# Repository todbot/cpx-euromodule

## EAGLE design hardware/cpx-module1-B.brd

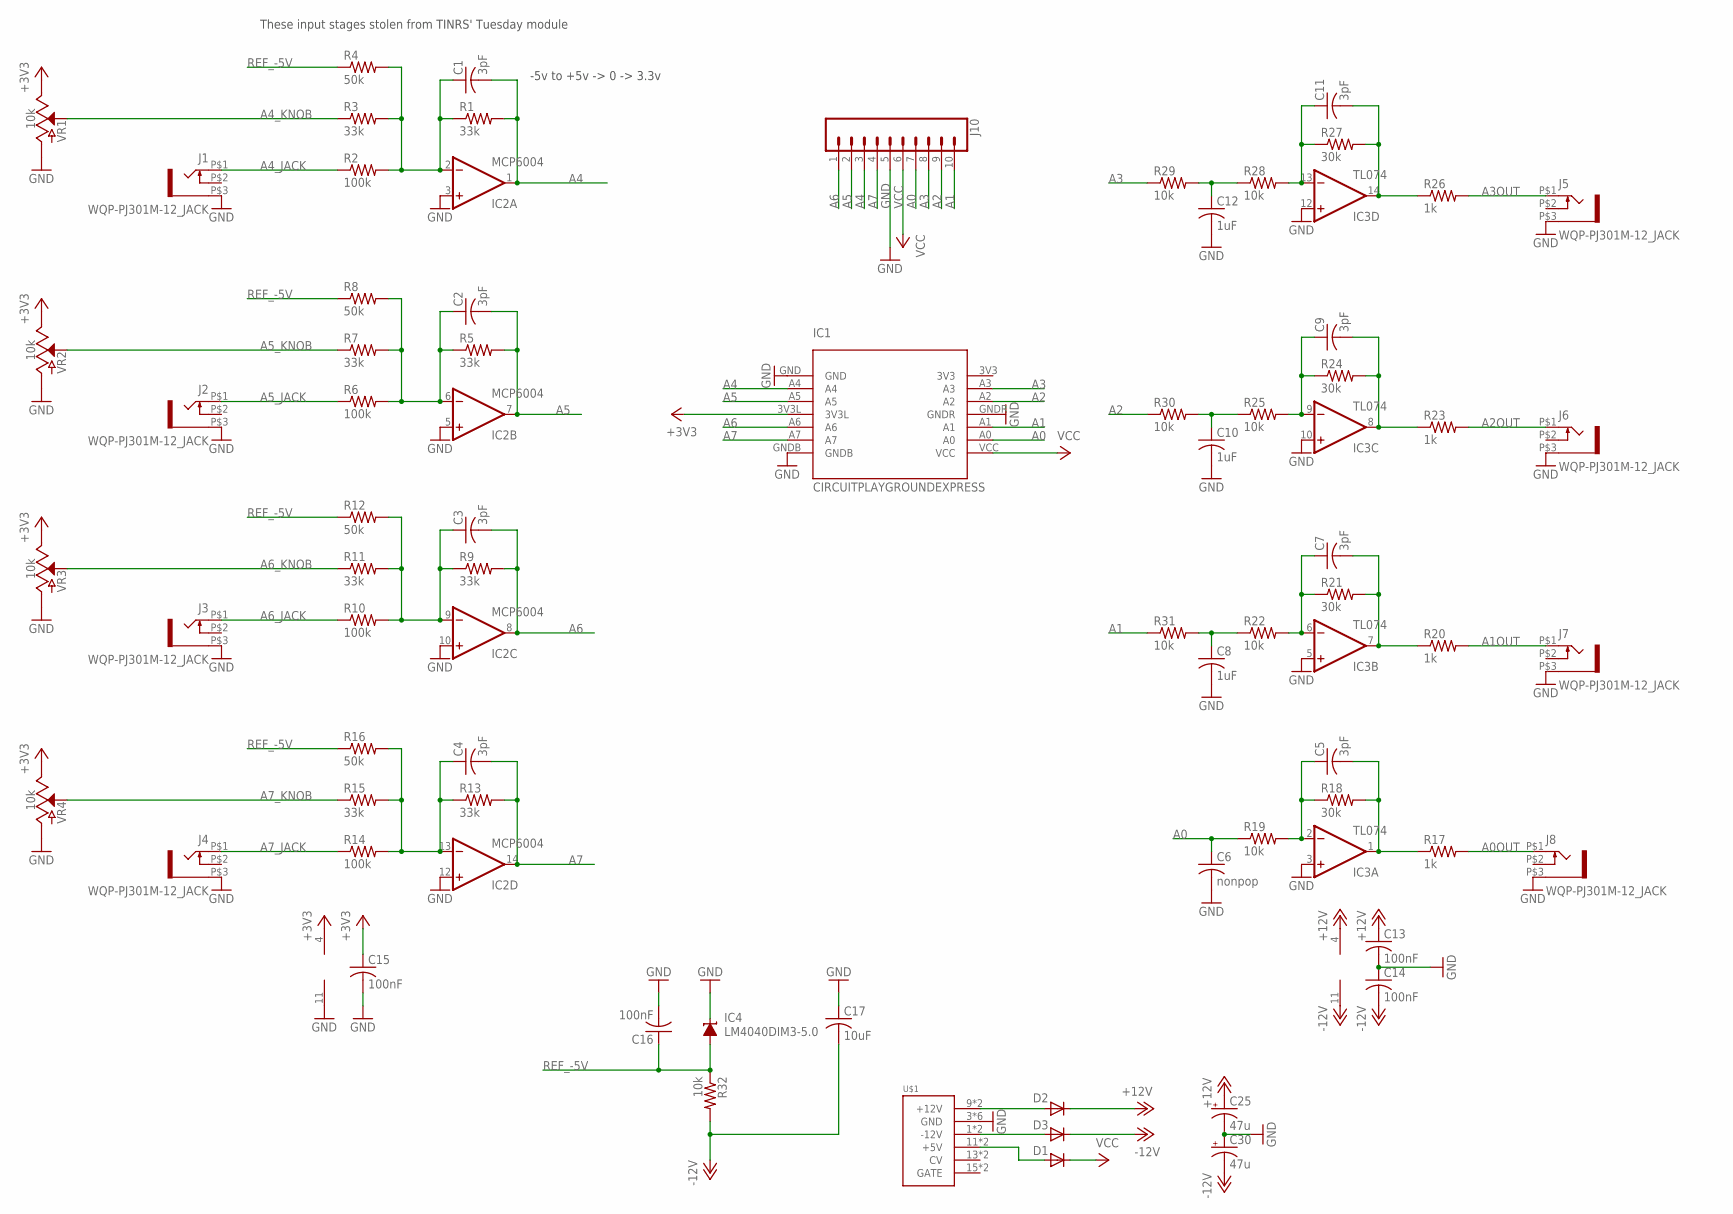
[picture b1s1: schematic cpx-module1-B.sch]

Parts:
C1, C2, C3, C4, C5, C7, C9, C11: 3pF; C0603
C6: nonpop; C0603
C8, C10, C12: 1uF; C0603
C13, C14, C15, C16: 100nF; C0603
C17: 10uF; C0603
C25, C30: 47u; PANASONIC_D
D1, D2, D3: 1N5819HW; SOD123
IC1: CIRCUITPLAYGROUNDEXPRESS
IC2: MCP6004; SO14
IC3: TL074; SO14
IC4: LM4040DIM3-5.0; DBZ_R-PDSO-G3
J1, J2, J3, J4, J5, J6, J7, J8: WQP-PJ301M-12_JACK
J10: CONN_10"; 1X10
R1, R3, R5, R7, R9, R11, R13, R15: 33k; R0603
R2, R6, R10, R14: 100k; R0603
R4, R8, R12, R16: 50k; R0603
R17, R20, R23, R26: 1k; R0603
R18, R21, R24, R27: 30k; R0603
R19, R22, R25, R28, R29, R30, R31, R32: 10k; R0603
U$1: POWER; POWER_16
VR1, VR2, VR3, VR4: 10k; POT-PTH-ALPS-KIT

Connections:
+3V3: C15.1, IC1.3V3L, IC2.4 (V+), VR1.P$1 (E), VR2.P$1 (E), VR3.P$1 (E), VR4.P$1 (E)
+12V: C13.1, C25.+, D2.C, IC3.4 (V+)
-12V: C14.2, C17.2, C30.-, D3.C, IC3.11 (V-), R32.2
A0: C6.1, IC1.A0, J10.7, R19.1
A0OUT: J8.P$1 (2), R17.2
A1: IC1.A1, J10.10, R31.1
A1OUT: J7.P$1 (2), R20.2
A2: IC1.A2, J10.9, R30.1
A2OUT: J6.P$1 (2), R23.2
A3: IC1.A3, J10.8, R29.1
A3OUT: J5.P$1 (2), R26.2
A4: C1.2, IC1.A4, IC2.1 (OUT), J10.3, R1.2
A4_JACK: J1.P$1 (2), R2.1
A4_KNOB: R3.1, VR1.P$2 (S)
A5: C2.2, IC1.A5, IC2.7 (OUT), J10.2, R5.2
A5_JACK: J2.P$1 (2), R6.1
A5_KNOB: R7.1, VR2.P$2 (S)
A6: C3.2, IC1.A6, IC2.8 (OUT), J10.1, R9.2
A6_JACK: J3.P$1 (2), R10.1
A6_KNOB: R11.1, VR3.P$2 (S)
A7: C4.2, IC1.A7, IC2.14 (OUT), J10.4, R13.2
A7_JACK: J4.P$1 (2), R14.1
A7_KNOB: R15.1, VR4.P$2 (S)
GND: C6.2, C8.2, C10.2, C12.2, C13.2, C14.1, C15.2, C16.2, C17.1, C25.-, C30.+, IC1.GND, IC1.GNDB, IC1.GNDR, IC2.3 (+IN), IC2.5 (+IN), IC2.10 (+IN), IC2.11 (V-), IC2.12 (+IN), IC3.3 (+IN), IC3.5 (+IN), IC3.10 (+IN), IC3.12 (+IN), IC4.1 (C), J1.P$3 (1), J2.P$3 (1), J3.P$3 (1), J4.P$3 (1), J5.P$3 (1), J6.P$3 (1), J7.P$3 (1), J8.P$3 (1), J10.5, U$1.3 (GND), U$1.4 (GND), U$1.5 (GND), U$1.6 (GND), U$1.7 (GND), U$1.8 (GND), VR1.P$3 (A), VR2.P$3 (A), VR3.P$3 (A), VR4.P$3 (A)
unnamed: C5.2, IC3.1 (OUT), R17.1, R18.2
unnamed: C2.1, IC2.6 (-IN), R5.1, R6.2, R7.2, R8.2
unnamed: C3.1, IC2.9 (-IN), R9.1, R10.2, R11.2, R12.2
unnamed: C4.1, IC2.13 (-IN), R13.1, R14.2, R15.2, R16.2
unnamed: C1.1, IC2.2 (-IN), R1.1, R2.2, R3.2, R4.2
unnamed: C5.1, IC3.2 (-IN), R18.1, R19.2
unnamed: C7.2, IC3.7 (OUT), R20.1, R21.2
unnamed: C7.1, IC3.6 (-IN), R21.1, R22.2
unnamed: C9.2, IC3.8 (OUT), R23.1, R24.2
unnamed: C9.1, IC3.9 (-IN), R24.1, R25.2
unnamed: C11.2, IC3.14 (OUT), R26.1, R27.2
unnamed: C11.1, IC3.13 (-IN), R27.1, R28.2
unnamed: D2.A, U$1.9 (+12V), U$1.10 (+12V)
unnamed: D3.A, U$1.1 (-12V), U$1.2 (-12V)
unnamed: D1.A, U$1.11 (+5V), U$1.12 (+5V)
unnamed: C12.1, R28.1, R29.2
unnamed: C10.1, R25.1, R30.2
unnamed: C8.1, R22.1, R31.2
REF_-5V: C16.1, IC4.2 (A), R4.1, R8.1, R12.1, R16.1, R32.1
VCC: D1.C, IC1.VCC, J10.6

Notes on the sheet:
-5v to +5v -> 0 -> 3.3v
These input stages stolen from TINRS' Tuesday module

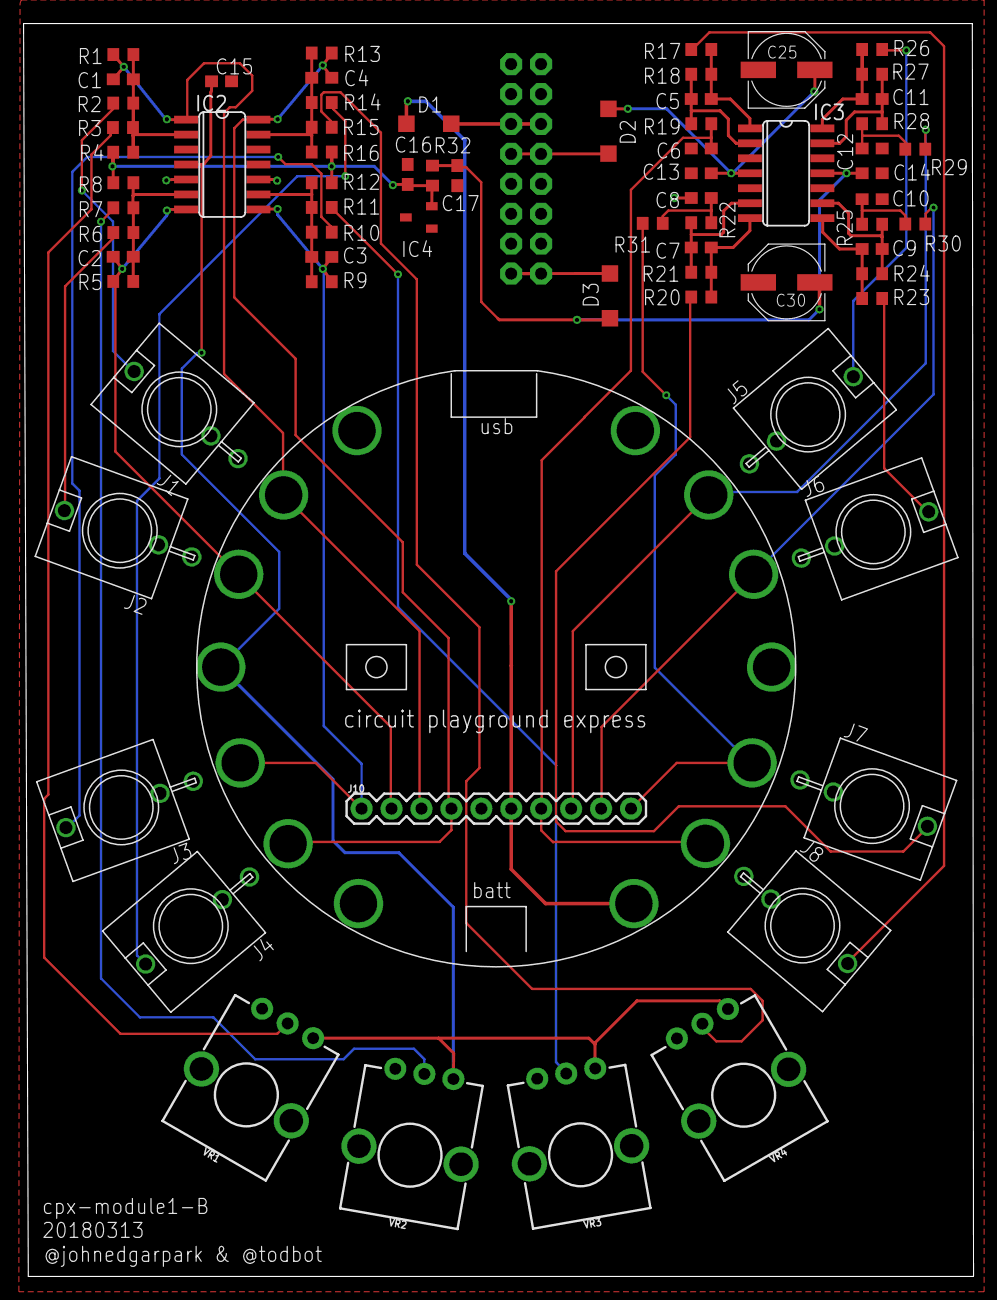
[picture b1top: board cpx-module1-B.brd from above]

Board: 2 copper layers, 80.6 x 106.3 mm, 72 parts (1 on the bottom side), 44 nets.

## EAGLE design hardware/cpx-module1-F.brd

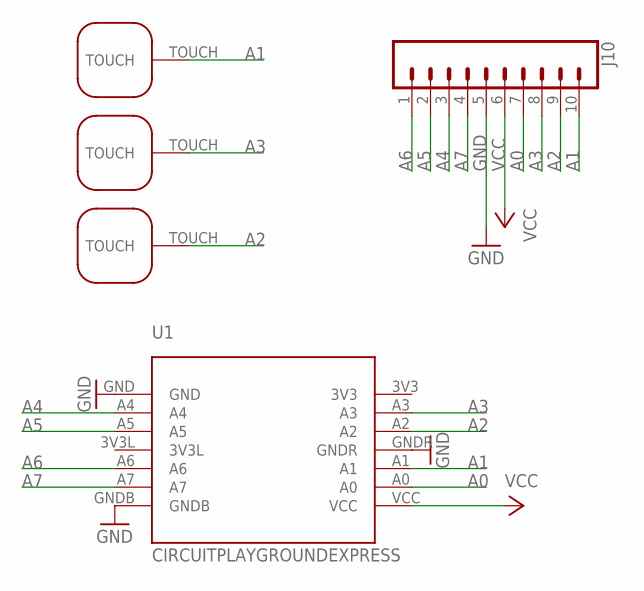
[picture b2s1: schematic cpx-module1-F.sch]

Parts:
J10: CONN_10"; 1X10
T1, T2, T4: TOUCHPADROUND1; TOUCHPAD1
U1: CIRCUITPLAYGROUNDEXPRESS

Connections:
A0: J10.7, U1.A0
A1: J10.10, T2.TOUCH, U1.A1
A2: J10.9, T4.TOUCH, U1.A2
A3: J10.8, T1.TOUCH, U1.A3
A4: J10.3, U1.A4
A5: J10.2, U1.A5
A6: J10.1, U1.A6
A7: J10.4, U1.A7
GND: J10.5, U1.GND, U1.GNDB, U1.GNDR
VCC: J10.6, U1.VCC

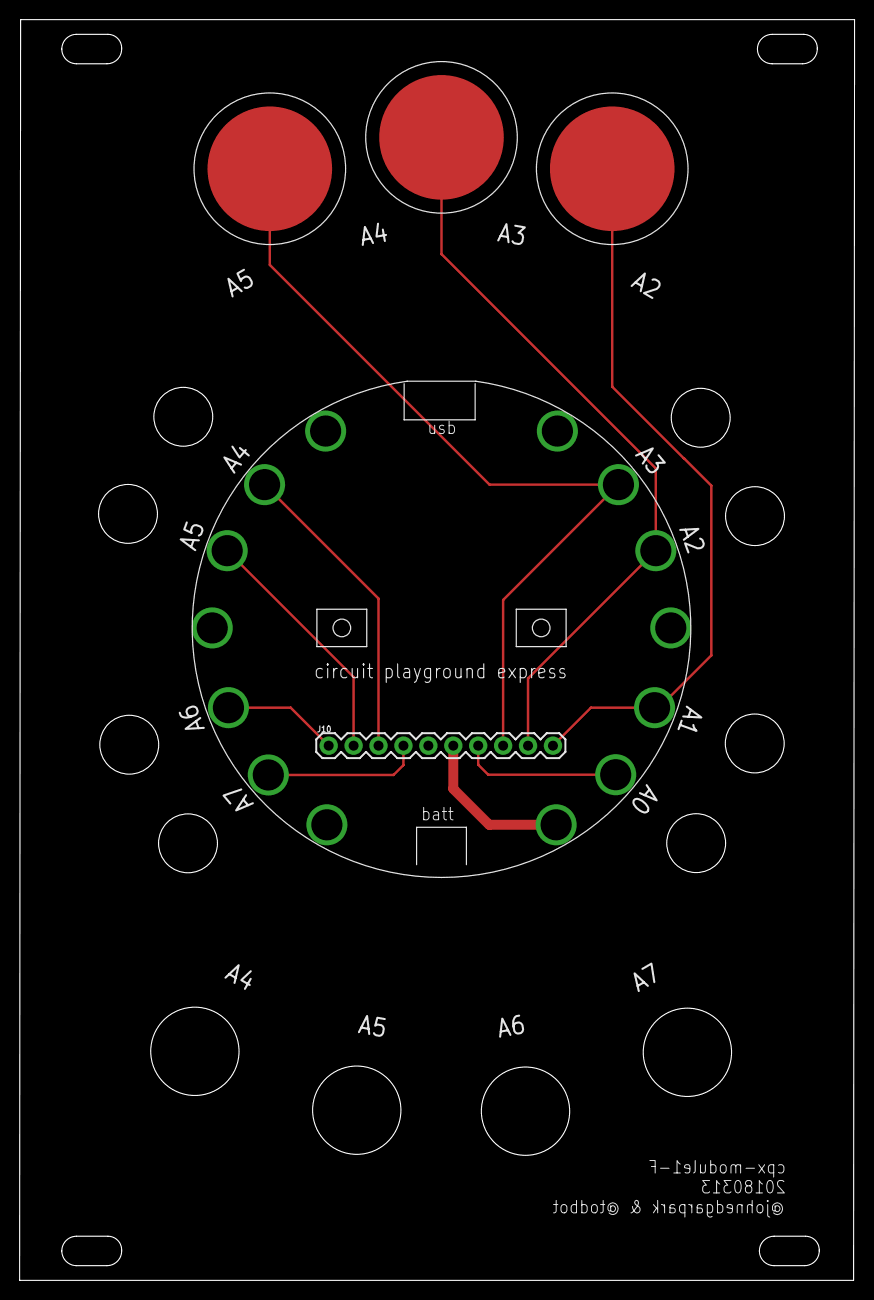
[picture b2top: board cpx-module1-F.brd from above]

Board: 2 copper layers, 85.1 x 128.5 mm, 5 parts (0 on the bottom side), 10 nets.

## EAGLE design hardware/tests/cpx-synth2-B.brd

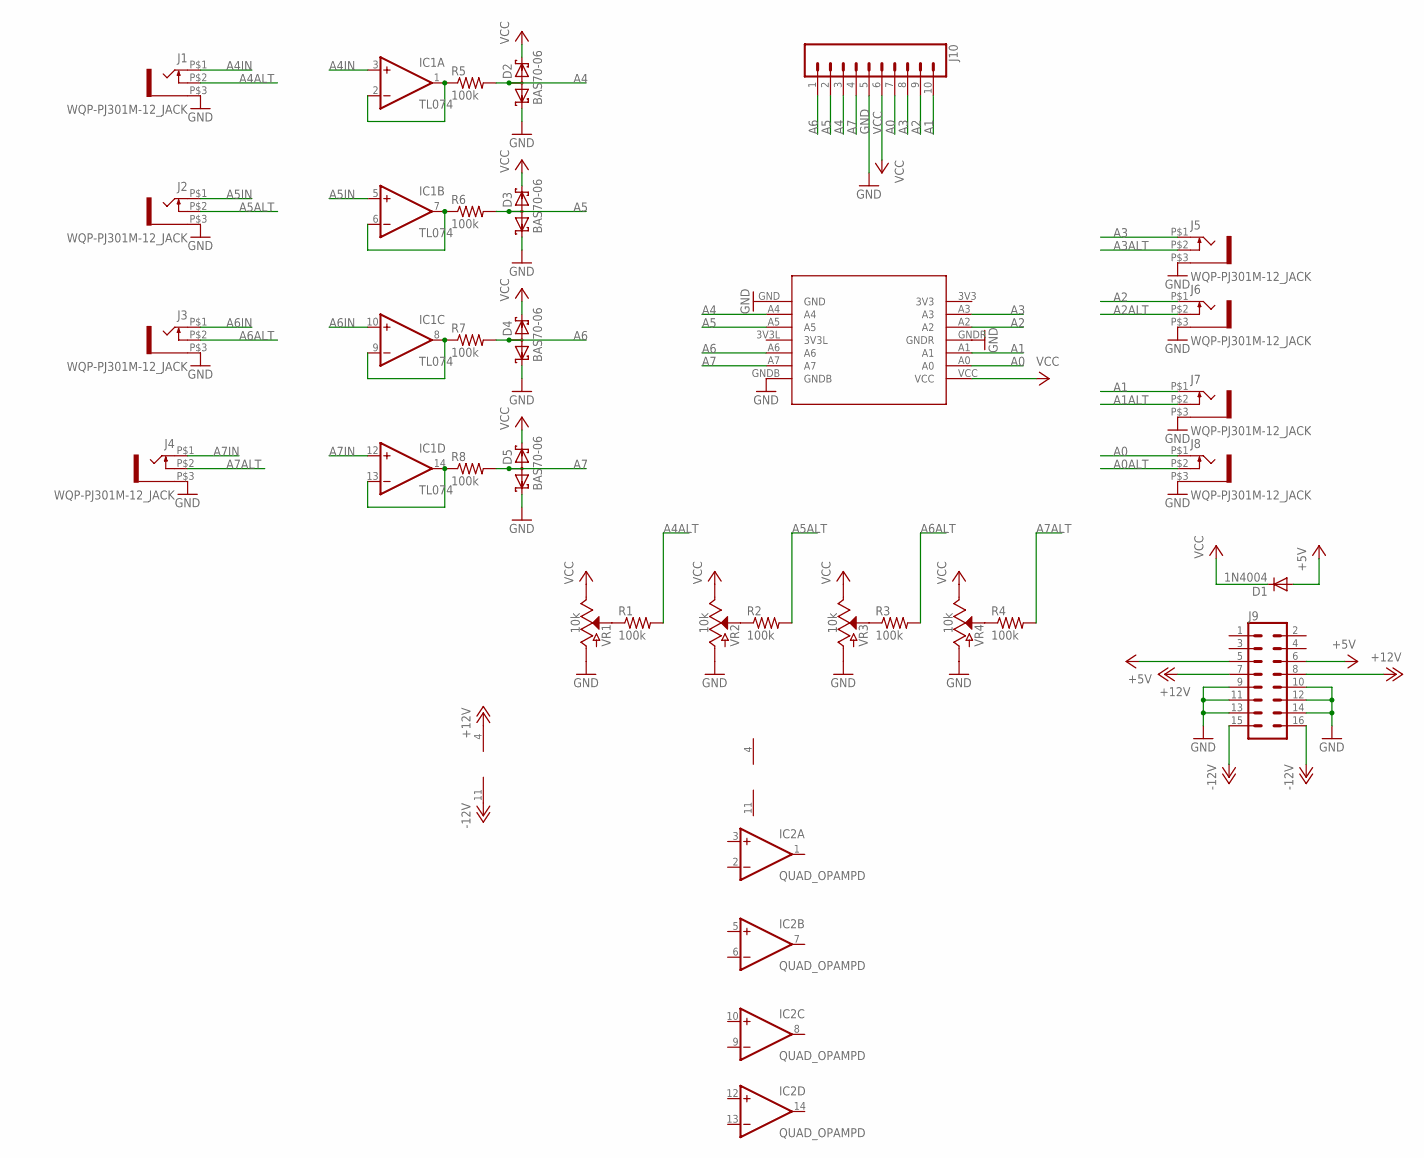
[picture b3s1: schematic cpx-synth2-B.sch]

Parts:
D1: 1N4004; DO41-10
D2, D3, D4, D5: BAS70-06; SOT23
IC1: TL074; SO14
IC2: QUAD_OPAMPD; SO14
J1, J2, J3, J4, J5, J6, J7, J8: WQP-PJ301M-12_JACK
J9: CONN_08X2; 2X8
J10: CONN_10"; 1X10
R1, R2, R3, R4, R5, R6, R7, R8: 100k; R0603
U1: CIRCUITPLAYGROUNDEXPRESS
VR1, VR2, VR3, VR4: 10k; POT-PTH-ALPS-KIT

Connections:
+5V: D1.A, J9.5, J9.6
+12V: IC1.4 (V+), J9.7, J9.8
-12V: IC1.11 (V-), J9.15, J9.16
A0: J8.P$1 (2), J10.7, U1.A0
A0ALT: J8.P$2 (3)
A1: J7.P$1 (2), J10.10, U1.A1
A1ALT: J7.P$2 (3)
A2: J6.P$1 (2), J10.9, U1.A2
A2ALT: J6.P$2 (3)
A3: J5.P$1 (2), J10.8, U1.A3
A3ALT: J5.P$2 (3)
A4: D2.3 (AA), J10.3, R5.2, U1.A4
A4ALT: J1.P$2 (3), R1.2
A4IN: IC1.3 (+IN), J1.P$1 (2)
A5: D3.3 (AA), J10.2, R6.2, U1.A5
A5ALT: J2.P$2 (3), R2.2
A5IN: IC1.5 (+IN), J2.P$1 (2)
A6: D4.3 (AA), J10.1, R7.2, U1.A6
A6ALT: J3.P$2 (3), R3.2
A6IN: IC1.10 (+IN), J3.P$1 (2)
A7: D5.3 (AA), J10.4, R8.2, U1.A7
A7ALT: J4.P$2 (3), R4.2
A7IN: IC1.12 (+IN), J4.P$1 (2)
GND: D2.1 (K1), D3.1 (K1), D4.1 (K1), D5.1 (K1), J1.P$3 (1), J2.P$3 (1), J3.P$3 (1), J4.P$3 (1), J5.P$3 (1), J6.P$3 (1), J7.P$3 (1), J8.P$3 (1), J9.9, J9.10, J9.11, J9.12, J9.13, J9.14, J10.5, U1.GND, U1.GNDB, U1.GNDR, VR1.P$3 (A), VR2.P$3 (A), VR3.P$3 (A), VR4.P$3 (A)
unnamed: R1.1, VR1.P$2 (S)
unnamed: R2.1, VR2.P$2 (S)
unnamed: R3.1, VR3.P$2 (S)
unnamed: R4.1, VR4.P$2 (S)
unnamed: IC1.6 (-IN), IC1.7 (OUT), R6.1
unnamed: IC1.8 (OUT), IC1.9 (-IN), R7.1
unnamed: IC1.1 (OUT), IC1.2 (-IN), R5.1
unnamed: IC1.13 (-IN), IC1.14 (OUT), R8.1
V+: IC2.4 (V+)
V-: IC2.11 (V-)
VCC: D1.C, D2.2 (K2), D3.2 (K2), D4.2 (K2), D5.2 (K2), J10.6, U1.VCC, VR1.P$1 (E), VR2.P$1 (E), VR3.P$1 (E), VR4.P$1 (E)

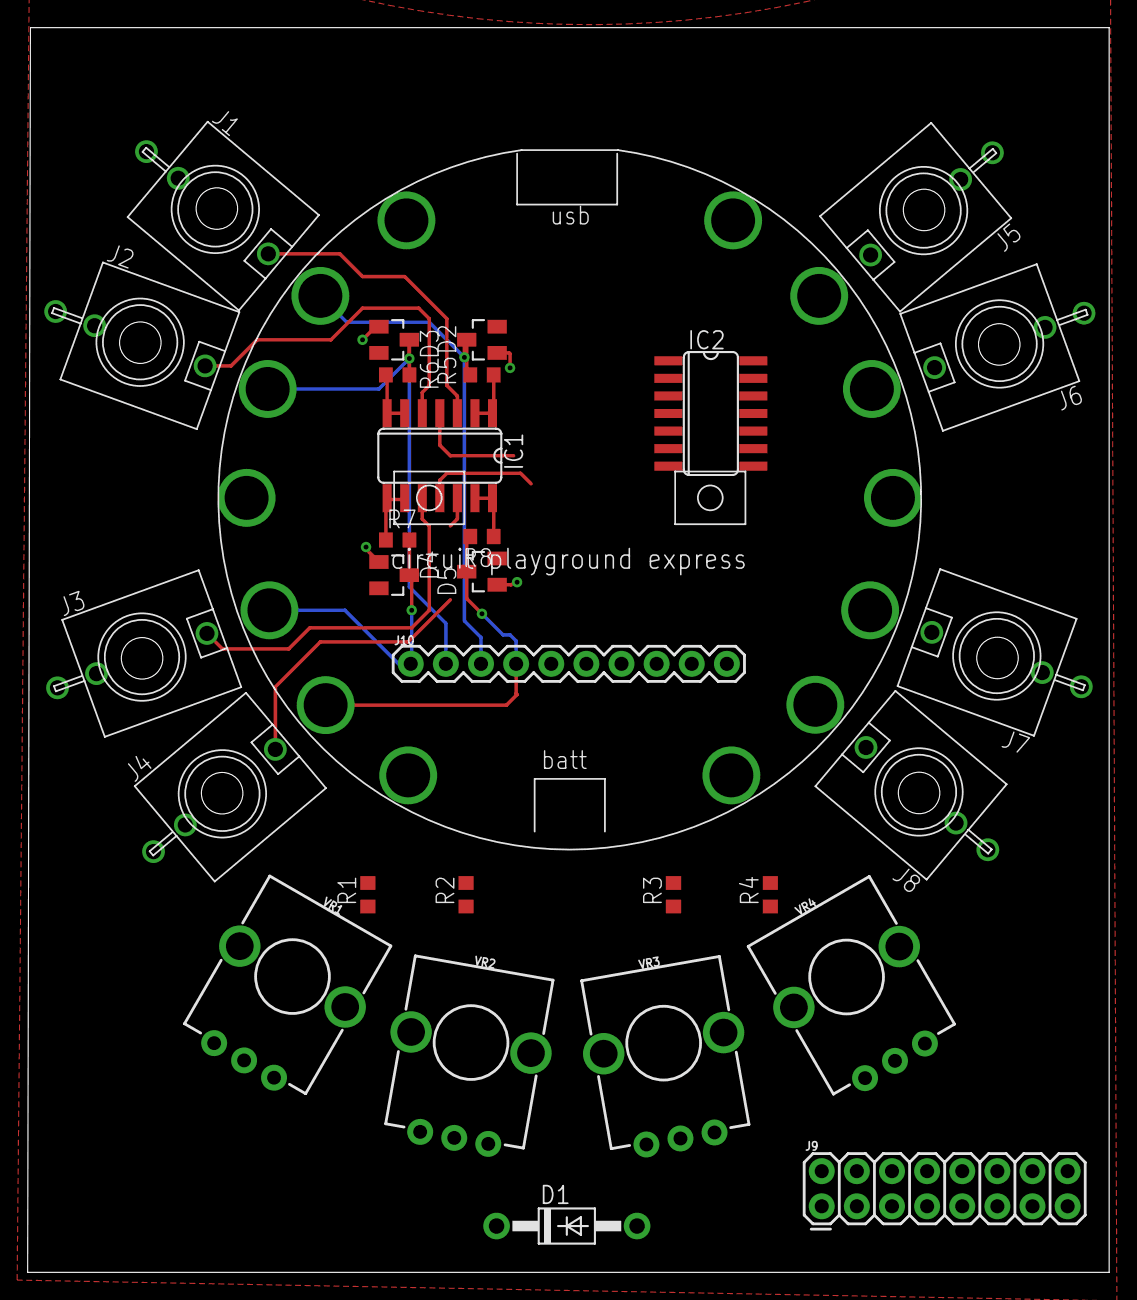
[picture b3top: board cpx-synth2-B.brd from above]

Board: 2 copper layers, 78.2 x 90.0 mm, 30 parts (0 on the bottom side), 29 nets.

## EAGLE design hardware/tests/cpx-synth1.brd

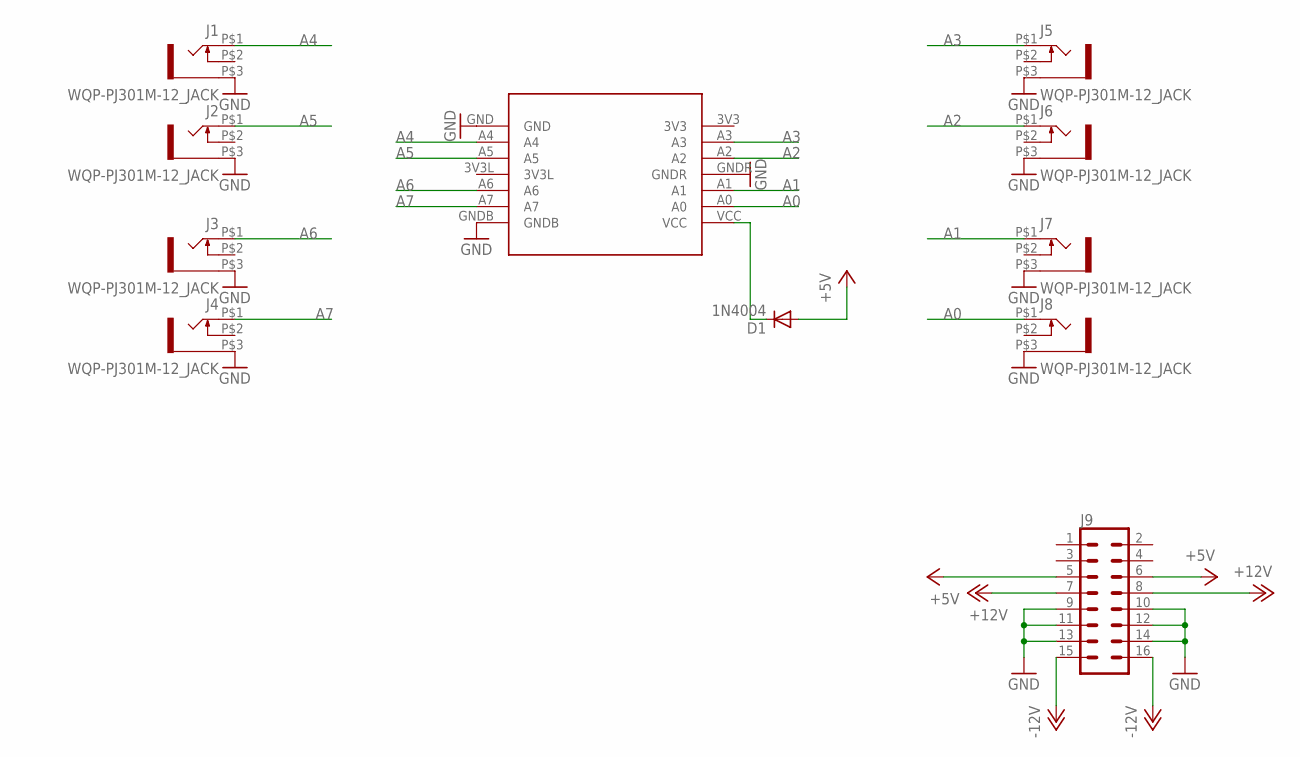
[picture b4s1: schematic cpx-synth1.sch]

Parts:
D1: 1N4004; DO41-10
J1, J2, J3, J4, J5, J6, J7, J8: WQP-PJ301M-12_JACK
J9: CONN_08X2; 2X8
U1: CIRCUITPLAYGROUNDEXPRESS

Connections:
+5V: D1.A, J9.5, J9.6
+12V: J9.7, J9.8
-12V: J9.15, J9.16
A0: J8.P$1 (2), U1.A0
A1: J7.P$1 (2), U1.A1
A2: J6.P$1 (2), U1.A2
A3: J5.P$1 (2), U1.A3
A4: J1.P$1 (2), U1.A4
A5: J2.P$1 (2), U1.A5
A6: J3.P$1 (2), U1.A6
A7: J4.P$1 (2), U1.A7
GND: J1.P$3 (1), J2.P$3 (1), J3.P$3 (1), J4.P$3 (1), J5.P$3 (1), J6.P$3 (1), J7.P$3 (1), J8.P$3 (1), J9.9, J9.10, J9.11, J9.12, J9.13, J9.14, U1.GND, U1.GNDB, U1.GNDR
unnamed: D1.C, U1.VCC

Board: 2 copper layers, 11 parts (0 on the bottom side), 13 nets, no tracks yet.

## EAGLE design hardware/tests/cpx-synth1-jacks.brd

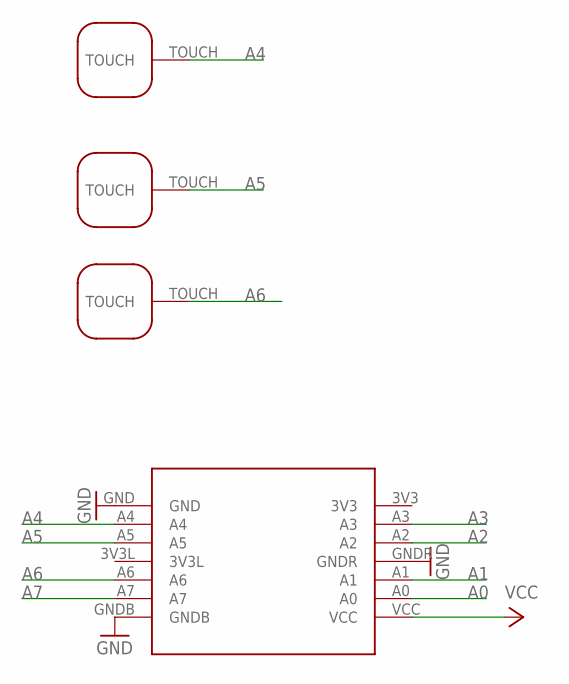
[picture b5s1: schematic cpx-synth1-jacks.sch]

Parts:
T1, T2, T3: TOUCHPADROUND1; TOUCHPAD1
U1: CIRCUITPLAYGROUNDEXPRESS

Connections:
A0: U1.A0
A1: U1.A1
A2: U1.A2
A3: U1.A3
A4: T3.TOUCH, U1.A4
A5: T2.TOUCH, U1.A5
A6: T1.TOUCH, U1.A6
A7: U1.A7
GND: U1.GND, U1.GNDB, U1.GNDR
VCC: U1.VCC

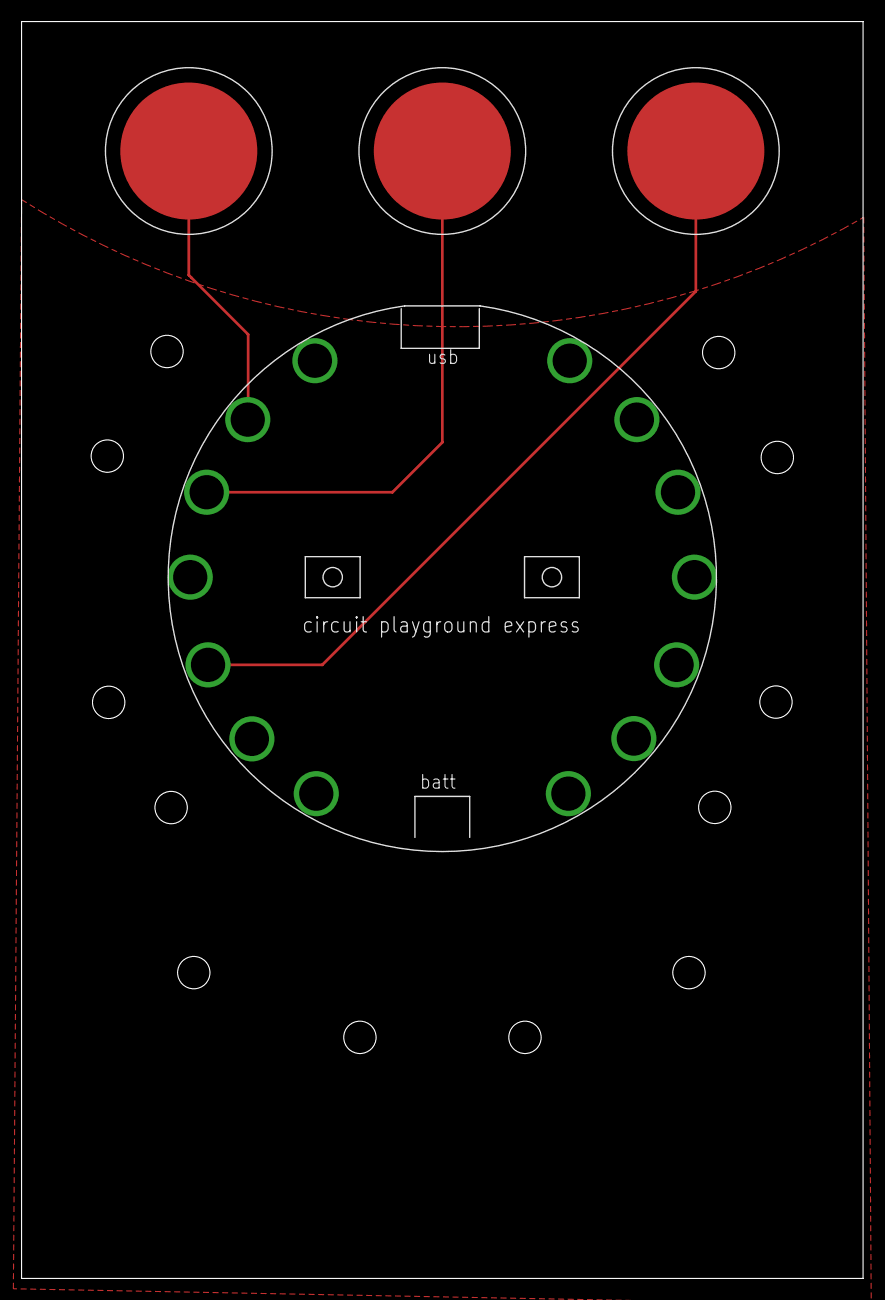
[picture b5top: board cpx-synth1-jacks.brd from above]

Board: 2 copper layers, 78.0 x 116.5 mm, 4 parts (0 on the bottom side), 4 nets.

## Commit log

2018-03-12 saving some progress
2018-03-12 fixed broken stuff
2018-03-12 first cut at component placement
2018-03-13 autorouted as a test
2018-03-13 better routing: hand-routed around opamp, autoroute to connectors
2018-03-13 added protection diodes and filter caps, added pdfs
2018-03-13 added resistors on A1,A2,A3 to potentially allow touch input to work, re-routed lower half a bit better
2018-03-14 fix silkscreen a little

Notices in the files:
parts and their libraries:
SparkFun-Connectors: Licensing: Creative Commons ShareAlike 4.0 International - https://creativecommons.org/licenses/by-sa/4.0
